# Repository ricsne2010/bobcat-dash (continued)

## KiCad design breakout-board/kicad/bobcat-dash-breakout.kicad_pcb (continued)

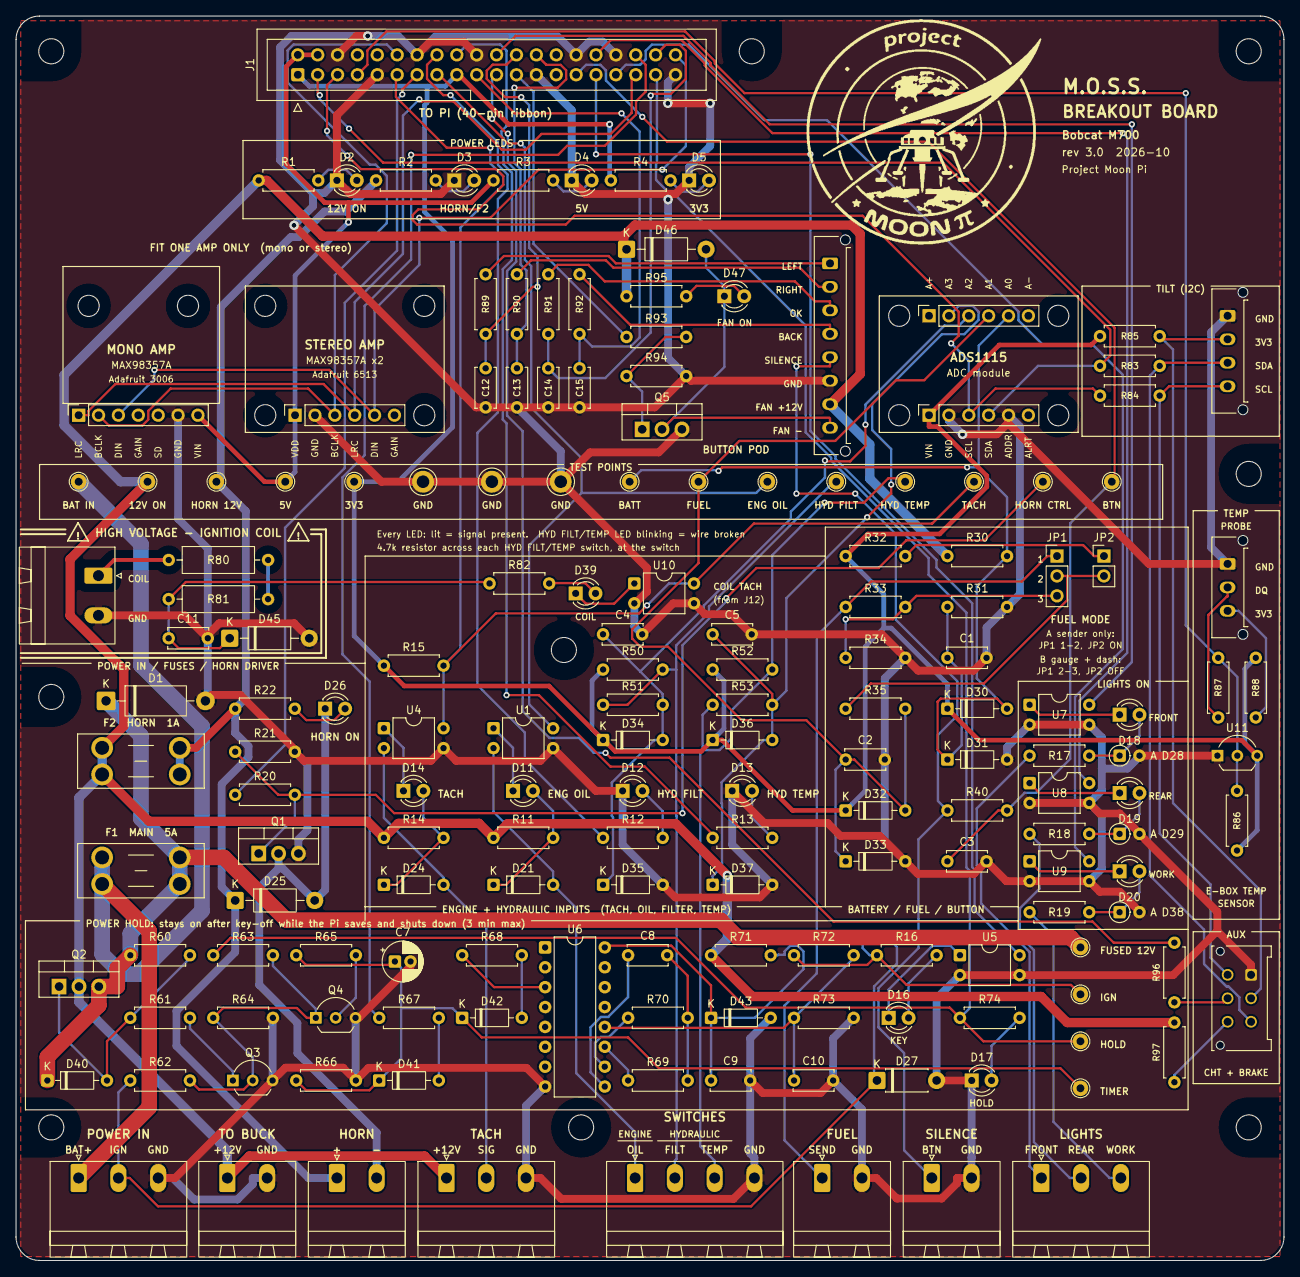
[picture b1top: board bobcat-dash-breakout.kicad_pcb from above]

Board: 2 copper layers, 162.0 x 159.0 mm, 187 parts (0 on the bottom side), 103 nets.

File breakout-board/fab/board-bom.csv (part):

"Refs","Value","Footprint","Qty","Description"
"C1,C2,C3,C4,C5,C9,C10,C12,C13,C14,C15","100nF","Capacitor_THT:C_Disc_D5.0mm_W2.5mm_P5.00mm","11","BACK button: debounce / noise filter,Debounce / noise filter,Decoupling,Filter,LEFT button: debounce / noise filter,OK button: debounce / noise filter,RIGHT button: debounce / noise filter"
"C7","10uF 25V","Capacitor_THT:CP_Radial_D5.0mm_P2.00mm","1","Stretches a power cut to a few seconds"
"C8","100nF film","Capacitor_THT:C_Disc_D5.0mm_W2.5mm_P5.00mm","1","Timing capacitor (film for accuracy)"
"C11","1uF 50V","Capacitor_THT:C_Disc_D5.0mm_W2.5mm_P5.00mm","1","Filters the coil's ringing: one clean pulse per spark (ceramic, X7R)"
"D1","P6KE20A","Diode_THT:D_DO-15_P12.70mm_Horizontal","1","TVS: clamps spikes, blows F1 if wired backwards"
"D2,D3,D4,D5,D17,D47","LED_green","LED_THT:LED_D3.0mm","6","+3.3V from Pi present,+5V from Pi present,Board powered (+12V switched on),Horn feed present (F2 OK),Pi is holding power on,Pod fan ON"
"D11,D12,D13,D14,D16,D18,D19,D20,D39","LED_yellow","LED_THT:LED_D3.0mm","9","Coil input: on while the coil is not charging, flickers with the engine,FILT: on = active, blink = wire fault (driven by the Pi),Front light on,Key on,OIL input active,Rear light on,TACH input active,TEMP: on = active, blink = wire fault (driven by the Pi),Work light on"
"D21,D24,D41,D42","1N4148","Diode_THT:D_DO-35_SOD27_P7.62mm_Horizontal","4","Pi KILL -> power cut,Reverse-spike protection across the LEDs,Timer -> power cut"
"D25,D46","1N4007","Diode_THT:D_DO-41_SOD81_P10.16mm_Horizontal","2","Flyback (coil horn / relay),Flyback (fan motor)"
"D26","LED_red","LED_THT:LED_D3.0mm","1","Horn output ON"
"D27","1N4007","Diode_THT:D_DO-41_SOD81_P7.62mm_Horizontal","1","Clamps negative spikes on the IGN wire"
"D28,D29,D38","1N4148","Diode_THT:D_DO-35_SOD27_P2.54mm_Vertical_AnodeUp","3","Reverse-spike protection across the LEDs (standing diode)"
"D30,D31,D32,D33,D34,D35,D36,D37","BAT85","Diode_THT:D_DO-35_SOD27_P7.62mm_Horizontal","8","Schottky clamp to 3.3V,Schottky clamp to GND"
"D40","BZX79C15","Diode_THT:D_DO-35_SOD27_P7.62mm_Horizontal","1","15 V zener: limits gate-source voltage"
"D43","BZX79C10","Diode_THT:D_DO-35_SOD27_P7.62mm_Horizontal","1","10 V supply for U6"
"D45","1N4744A","Diode_THT:D_DO-41_SOD81_P10.16mm_Horizontal","1","15 V 1 W zener: clamps the coil spike (and negative ringing to -0.7 V)"
"F1","5A","Fuse:Fuseholder_Blade_Mini_Keystone_3568","1","Mini blade fuse: main feed"
"F2","1A","Fuse:Fuseholder_Blade_Mini_Keystone_3568","1","Mini blade fuse: horn"
"J1","TO PI (40-pin ribbon)","Connector_IDC:IDC-Header_2x20_P2.54mm_Vertical","1","Box header, straight 40-pin IDC ribbon to the Pi GPIO header"
"J2","POWER IN","Connector_Phoenix_MSTB:PhoenixContact_MSTBA_2,5_3-G-5,08_1x03_P5.08mm_Horizontal","1","Constant battery +12V (fused at the battery), key switch IGN signal, chassis ground"
"J3","TO 5V BUCK","Connector_Phoenix_MSTB:PhoenixContact_MSTBA_2,5_2-G-5,08_1x02_P5.08mm_Horizontal","1","Switched, fused +12V out to the 12V->5V buck"
"J4","SWITCHES","Connector_Phoenix_MSTB:PhoenixContact_MSTBA_2,5_4-G-5,08_1x04_P5.08mm_Horizontal","1","Engine oil pressure, hydraulic filter bypass, hydraulic oil temp switch wires"
"J5","TACH","Connector_Phoenix_MSTB:PhoenixContact_MSTBA_2,5_3-G-5,08_1x03_P5.08mm_Horizontal","1","Hall sensor (brown +12V, black SIG, blue GND), if used instead of the coil input"
"J6","FUEL","Connector_Phoenix_MSTB:PhoenixContact_MSTBA_2,5_2-G-5,08_1x02_P5.08mm_Horizontal","1","Fuel sender"
"J7","HORN","Connector_Phoenix_MSTB:PhoenixContact_MSTBA_2,5_2-G-5,08_1x02_P5.08mm_Horizontal","1","Piezo alarm + and -"
"J8","SILENCE","Connector_Phoenix_MSTB:PhoenixContact_MSTBA_2,5_2-G-5,08_1x02_P5.08mm_Horizontal","1","Silence push button"
"J9","MAX98357A MONO","Connector_PinSocket_2.54mm:PinSocket_1x07_P2.54mm_Vertical","1","Socket for the mono MAX98357A I2S amp board (Adafruit 3006): LRC BCLK DIN GAIN SD GND VIN"
"J10","ADS1115 PWR/I2C","Connector_PinSocket_2.54mm:PinSocket_1x06_P2.54mm_Vertical","1","Socket for the ADS1115 board's bottom row: VIN GND SCL SDA ADDR ALRT (ADDR to GND: address 0x48)"
"J11","LIGHTS","Connector_Phoenix_MSTB:PhoenixContact_MSTBA_2,5_3-G-5,08_1x03_P5.08mm_Horizontal","1","Sense wires from the lamp side of the front / rear / work light switches (a few mA each)"
"J12","COIL","Connector_Phoenix_MSTB:PhoenixContact_MSTBA_2,5_2-G-5,08_1x02_P5.08mm_Horizontal","1","Ignition coil NEGATIVE terminal (high voltage spikes) + GND for a shielded wire's drain (rev 2.4)"
"J13","TILT","Connector_Molex:Molex_Micro-Fit_3.0_43650-0415_1x04_P3.00mm_Vertical","1","Molex Micro-Fit 3.0 43650-0415 (latching). Mates with housing 43645-0400 + 43030-0007 pins. Tilt sensor: GND, 3V3, SDA, SCL; cable under ~30-50 cm"
"J14","TEMP PROBE","Connector_Molex:Molex_Micro-Fit_3.0_43650-0315_1x03_P3.00mm_Vertical","1","Molex Micro-Fit 3.0 43650-0315 (latching): external DS18B20 probes: 1 GND, 2 DQ, 3 3V3. Housing 43645-0300"
"J15","ADS1115 INPUTS","Connector_PinSocket_2.54mm:PinSocket_1x06_P2.54mm_Vertical","1","Socket for the ADS1115 board's top row: A+ A3 A2 A1 A0 A-"
"J16","MAX98357A STEREO","Connector_PinSocket_2.54mm:PinSocket_1x06_P2.54mm_Vertical","1","Socket for the stereo MAX98357A amp board (Adafruit 6513): VDD GND BCLK LRC DIN GAIN. Fit J9 or J16, not both"
"J17","POD","Connector_Molex:Molex_Micro-Fit_3.0_43650-0815_1x08_P3.00mm_Vertical","1","Latching Molex Micro-Fit 3.0 8-pin to the button pod: LEFT RIGHT OK BACK SILENCE GND FAN+ FAN-"
"J18","AUX (CHT + BRAKE)","Connector_Molex:Molex_Micro-Fit_3.0_43045-0612_2x03_P3.00mm_Vertical","1","Molex Micro-Fit 3.0 43045-0612 2x3 (latching): CHT board. 1 GND, 2 3V3, 3 SDA, 4 SCL, 5 BRAKE, 6 BRAKE 12V. Housing 43025-0600"
"JP1","A=1-2  B=2-3","Connector_PinHeader_2.54mm:PinHeader_1x03_P2.54mm_Vertical","1","Fuel mode select"
"JP2","PULL-UP (A only)","Connector_PinHeader_2.54mm:PinHeader_1x02_P2.54mm_Vertical","1","Fit for option A"
"Q1,Q5","IRLZ44N","Package_TO_SOT_THT:TO-220-3_Vertical","2","Logic-level MOSFET, low-side switch,Logic-level MOSFET: pod fan, low-side switch"
"Q2","IRF4905","Package_TO_SOT_THT:TO-220-3_Vertical","1","P-MOSFET high-side power switch, -55 V 74 A 20 mOhm"
"Q3,Q4","BC547B","Package_TO_SOT_THT:TO-92_Inline_Wide","2","Power cut: overrides key and HOLD,Turns Q2 on"
"R1,R2,R22,R95","3.3k","Resistor_THT:R_Axial_DIN0207_L6.3mm_D2.5mm_P7.62mm_Horizontal","4",""
"R3,R35,R40,R67,R68,R89,R90,R91,R92,R96","1k","Resistor_THT:R_Axial_DIN0207_L6.3mm_D2.5mm_P7.62mm_Horizontal","10","BACK button: series protection,LEFT button: series protection,OK button: series protection,Parking brake signal: series protection (GPIO 9),RIGHT button: series protection,Series,Series protection"
"R4,R12,R13,R71,R74,R82","470","Resistor_THT:R_Axial_DIN0207_L6.3mm_D2.5mm_P7.62mm_Horizontal","6","LED current,LED current, ~2 mA,Status LED current,Supply"
"R11,R14,R16,R17,R18,R19,R97","2.2k","Resistor_THT:R_Axial_DIN0207_L6.3mm_D2.5mm_P7.62mm_Horizontal","7","LED current, ~4 mA,Parking brake input LEDs on the CHT board, ~4 mA; a shorted cable draws ~5 mA"
"R15,R21,R31,R34,R51,R53,R63,R72,R94","10k","Resistor_THT:R_Axial_DIN0207_L6.3mm_D2.5mm_P7.62mm_Horizontal","9","Divider bottom,Divider bottom (option B),Keeps the fan off while the Pi boots,Key on -> timer reset,Pi HOLD -> power on,Pull-down: horn off while the Pi boots,Series protection,Tach pull-up (10k from rev 2.4: halves the current the PC817s must sink, for margin at low LED current)"
"R20,R83,R84,R87,R93","100","Resistor_THT:R_Axial_DIN0207_L6.3mm_D2.5mm_P7.62mm_Horizontal","5","Gate resistor,Probe data series protection,SCL series protection,SDA series protection"
"R30,R33,R60,R62","47k","Resistor_THT:R_Axial_DIN0207_L6.3mm_D2.5mm_P7.62mm_Horizontal","4","Divider top (option B),Divider top (ratio 5.7),Gate pull-up: Q2 off by default,Key on -> power on"
"R32","220","Resistor_THT:R_Axial_DIN0207_L6.3mm_D2.5mm_P7.62mm_Horizontal","1","Sender pull-up (option A)"
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
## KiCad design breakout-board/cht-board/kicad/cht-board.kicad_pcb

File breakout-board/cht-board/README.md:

# CHT + Parking Brake Board (rev 1.0)

A small board (87 × 46 mm) for the electronics box, on a short latching cable to the breakout board's
**AUX** plug (J18, breakout board rev 3.0). It carries:

- **Cylinder head temperatures (CHT):** up to four Adafruit **MCP9601** thermocouple amplifier modules
  (product 5165), one per cylinder, plugged into sockets. Fit only the ones you need.
- **Parking brake input:** the switch on the handle comes in on a 2-pin Phoenix plug, through an optocoupler,
  to the Pi (GPIO 9). Green **BRAKE SET** LED while the brake is set.

## Thermocouples

- Sensor: The Sensor Connection **CHT-FS-072-06-18-K-MP** (or -120- / custom 144 in lead): Type K, ungrounded,
  18 mm ring for the Wisconsin VH4D's plugs, rated to 1000 °C.
- Each module has its own 2-screw terminal: the Type K wire (or Type K extension wire) goes **straight into it**.
  That terminal is the cold junction, right beside the chip that measures it, so there's nothing in between.
  US colours: **yellow +, red −** (the module marks + and −).
- Only Type K extension wire and Type K (yellow) mini connectors between the sensor and the module. For the
  box wall, panel-mount mini K jacks, then a short piece of K wire inside to the module.

## Addresses

The socket sets each module's I2C address through its ADDR pin, the same way the module's own address jumpers
do, so **leave the modules' 22k / 43k jumpers open** and any module works in any socket:

| Socket | Cylinder | ADDR | Address | `config.toml` |
|---|---|---|---|---|
| M1 | 1 | to GND | 0x60 | `{ name = "1", address = 0x60 }` |
| M2 | 2 | 22k to GND (R1) | 0x65 | `{ name = "2", address = 0x65 }` |
| M3 | 3 | 43k to GND (R2) | 0x66 | `{ name = "3", address = 0x66 }` |
| M4 | 4 | open | 0x67 | `{ name = "4", address = 0x67 }` |

List the fitted ones in `[cht] cylinders`. With one sensor, put its module in the socket for that cylinder.

## Parking brake

`J2 PARK BRAKE`: **SW** and **GND**. A sealed switch on the handle that **closes when the brake is set**
(e.g. a sealed roller-lever microswitch, IP67, with a factory pigtail; a weather-sealed Deutsch DT 2-pin at the
handle). Then `[park_brake] enabled = true`. The 12 V comes from the breakout board through 2.2k (R97), so the
cable can't draw more than ~5 mA even shorted.

## Assembly

- Modules: solder the 9-pin header that comes with each module **pins down**, plug it into the socket, and screw
  its two holes down on **11 mm M2.5 standoffs** (the holes are on the terminal edge).
- Board: four **M3** corner holes. The AUX cable: two Molex Micro-Fit 3.0 2×3 housings (43025-0600) and
  six crimp pins (43030-0007), **pin 1 to pin 1** straight through.
- The modules' SDA / SCL each have a 10k pull-up; with four of them on the bus the total is still fine for the
  Pi's I2C at 100 kHz.

## Files

- `kicad/`: KiCad 10 project (schematic + board), made by `generator/` (`bash generator/build.sh`, reusing the
  breakout board's `route.py`).
- `fab/cht-board-gerbers.zip` for PCBWay (blue mask, like the breakout board), `fab/cht-board-bom.csv`.
- `docs/`: schematic PDF and renders.

Module pinout from Adafruit's design files (Adafruit-MCP9601-PCB, header JP3): VIN GND SCL SDA ALERT1-4 ADDR.

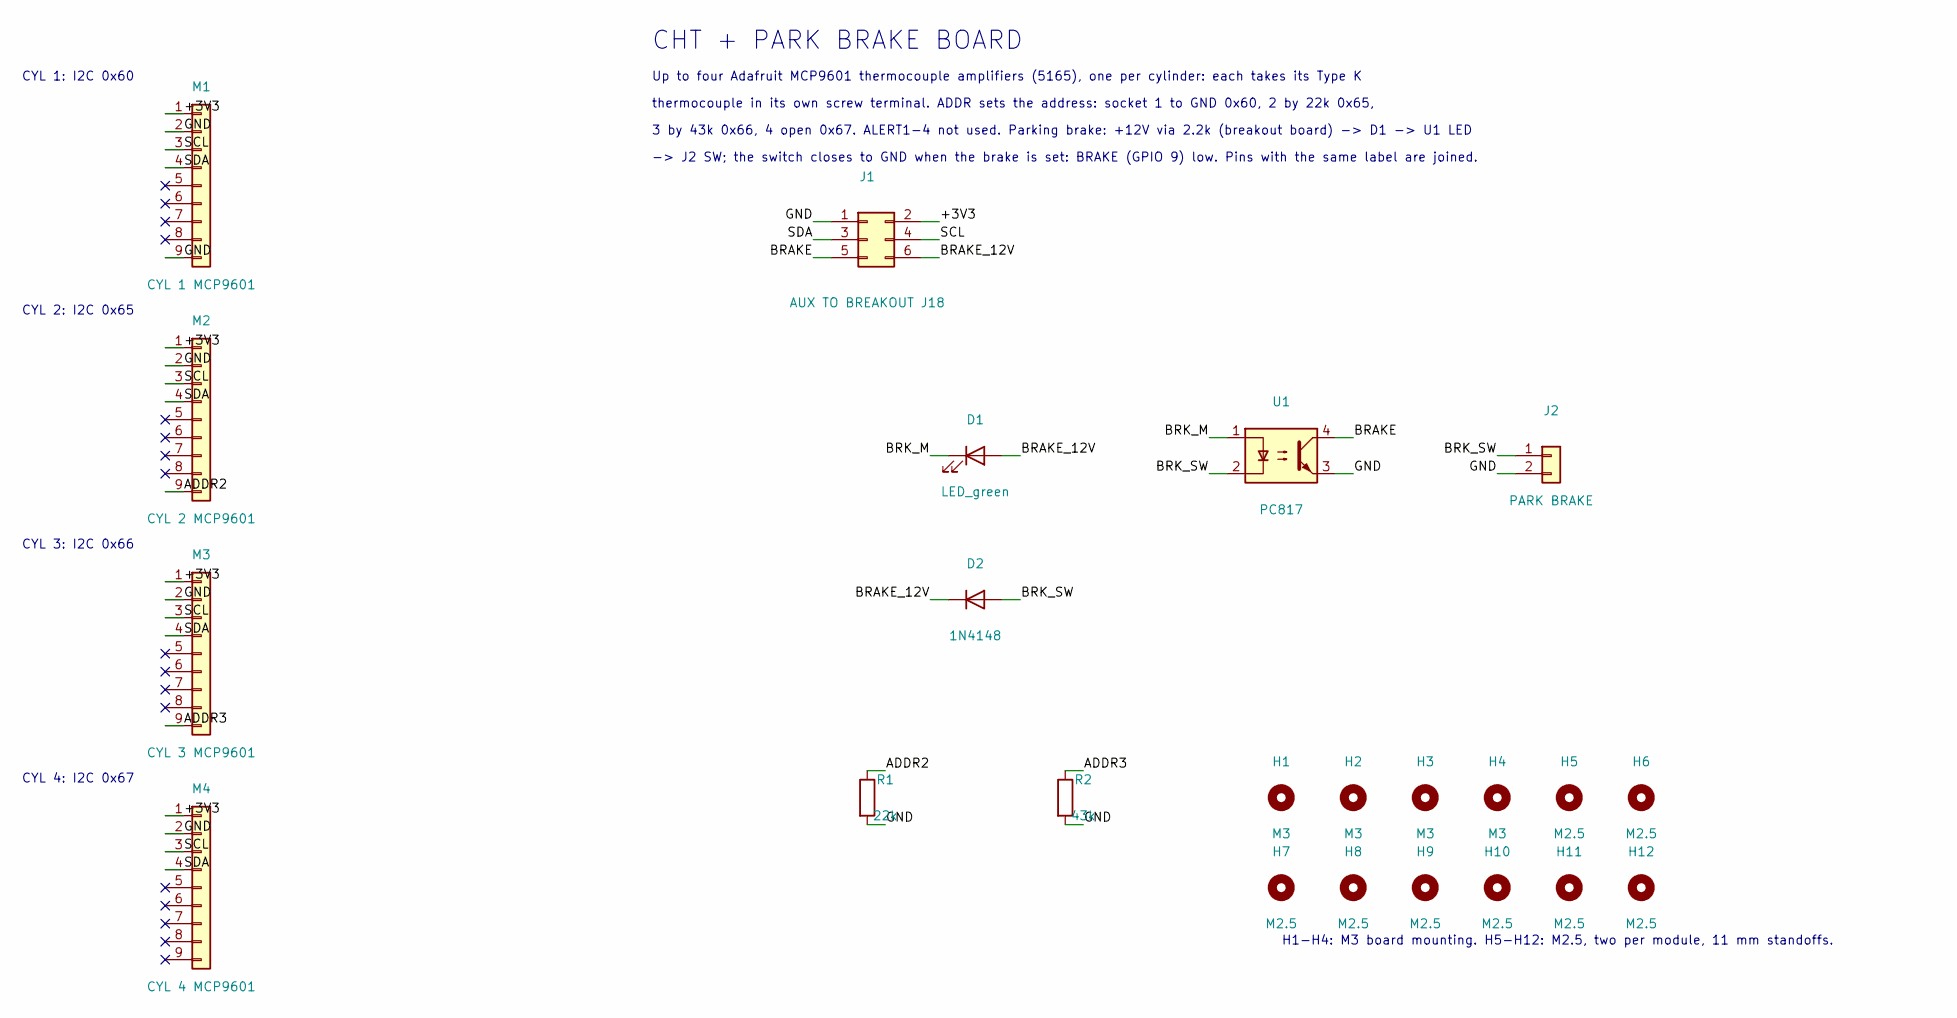
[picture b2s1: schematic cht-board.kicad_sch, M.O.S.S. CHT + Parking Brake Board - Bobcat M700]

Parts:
D1: LED_green; LED_D3.0mm
D2: 1N4148; D_DO-35_SOD27_P7.62mm_Horizontal
H1, H2, H3, H4: M3; MountingHole_3.2mm_M3
H5, H6, H7, H8, H9, H10, H11, H12: M2.5; MountingHole_2.7mm_M2.5
J1: AUX TO BREAKOUT J18; Molex_Micro-Fit_3.0_43045-0612_2x03_P3.00mm_Vertical
J2: PARK BRAKE; PhoenixContact_MSTBA_2,5_2-G-5,08_1x02_P5.08mm_Horizontal
M1: CYL 1 MCP9601; PinSocket_1x09_P2.54mm_Vertical
M2: CYL 2 MCP9601; PinSocket_1x09_P2.54mm_Vertical
M3: CYL 3 MCP9601; PinSocket_1x09_P2.54mm_Vertical
M4: CYL 4 MCP9601; PinSocket_1x09_P2.54mm_Vertical
R1: 22k; R_Axial_DIN0207_L6.3mm_D2.5mm_P7.62mm_Horizontal
R2: 43k; R_Axial_DIN0207_L6.3mm_D2.5mm_P7.62mm_Horizontal
U1: PC817; DIP-4_W7.62mm

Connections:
/+3V3: J1.2, M1.1, M2.1, M3.1, M4.1
/ADDR2: M2.9, R1.1
/ADDR3: M3.9, R2.1
/BRAKE: J1.5, U1.4
/BRAKE_12V: D1.2 (A), D2.1 (K), J1.6
/BRK_M: D1.1 (K), U1.1
/BRK_SW: D2.2 (A), J2.1, U1.2
/GND: J1.1, J2.2, M1.2, M1.9, M2.2, M3.2, M4.2, R1.2, R2.2, U1.3
/SCL: J1.4, M1.3, M2.3, M3.3, M4.3
/SDA: J1.3, M1.4, M2.4, M3.4, M4.4

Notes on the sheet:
CYL 1: I2C 0x60
CYL 2: I2C 0x65
CYL 3: I2C 0x66
CYL 4: I2C 0x67
CHT + PARK BRAKE BOARD
Up to four Adafruit MCP9601 thermocouple amplifiers (5165), one per cylinder: each takes its Type K
thermocouple in its own screw terminal. ADDR sets the address: socket 1 to GND 0x60, 2 by 22k 0x65,
3 by 43k 0x66, 4 open 0x67. ALERT1-4 not used. Parking brake: +12V via 2.2k (breakout board) -> D1 -> U1 LED
-> J2 SW; the switch closes to GND when the brake is set: BRAKE (GPIO 9) low. Pins with the same label are joined.
H1-H4: M3 board mounting. H5-H12: M2.5, two per module, 11 mm standoffs.

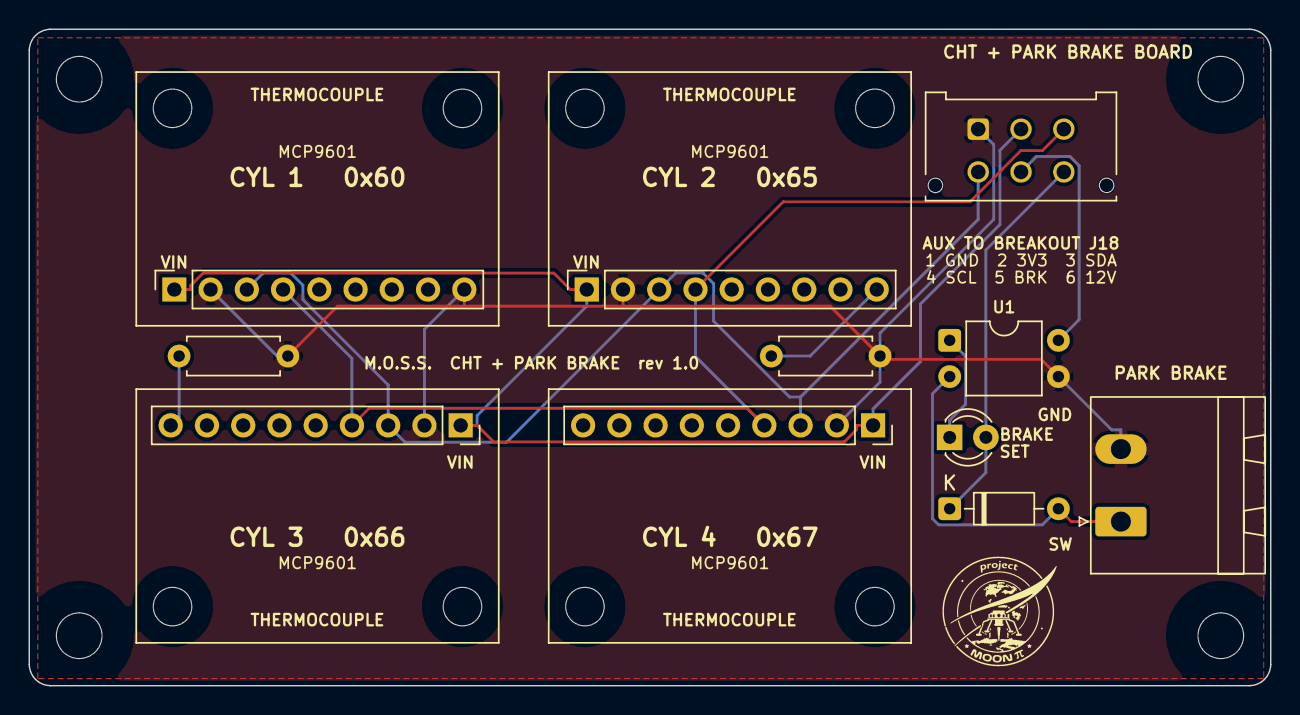
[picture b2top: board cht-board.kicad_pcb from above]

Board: 2 copper layers, 87.0 x 46.0 mm, 23 parts (0 on the bottom side), 10 nets.

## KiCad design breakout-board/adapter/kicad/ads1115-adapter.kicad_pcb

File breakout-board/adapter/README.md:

# ADS1115 Adapter (rev 1.1)

The breakout board (rev 2.8) takes the **current Adafruit ADS1115 (product 1085, STEMMA QT version)** directly:
two 6-pin rows 12.7 mm (0.5") apart, plugged into **J15** and **J10** and screwed down on H5–H8.

If that board isn't available, this adapter takes the other common ADS1115 layout: **one 10-pin row** in the order
`VDD GND SCL SDA ADDR ALRT A0 A1 A2 A3`. That's the older Adafruit 1085 and nearly every clone. Check the labels
on your module match that order before plugging it in.

- **Underneath:** male pins in the same two-row pattern as the Adafruit board (J1 into the breakout board's J15,
  J2 into its J10), and the same four M2.5 holes, so it sits on the same 11 mm standoffs.
- **On top:** a 10-pin female socket (J3) for the module, and two M2.5 holes (H5, H6) for the module's own
  mounting holes, so it's screwed down too, not just held by its pins. They match the original Adafruit 10-pin
  board (holes on its far edge, 12.7 mm from its pins, in line with pins 1 and 10). Clones vary: check yours.
- **Wiring is straight through:** same signals, same address (0x48: ADDR is grounded on the breakout board),
  **no software change**. A+ / A- of the two-row pattern aren't used.

| | |
|---|---|
| Size | 42 × 24.7 mm, 2 layers, 1.6 mm. The right-hand 12 mm carries the Project Moon Pi logo, top and back (beside the module, so it stays visible); on the breakout board it sits over the empty space between the ADC module and the TEMP column |
| Schematic | [docs/schematic.pdf](docs/schematic.pdf) |
| Gerbers | [fab/ads1115-adapter-gerbers.zip](fab/ads1115-adapter-gerbers.zip): order it with the main board (most makers sell 5 minimum for a few dollars) |
| KiCad files | [kicad/](kicad/) |

## Parts

| Qty | Part | Notes |
|---|---|---|
| 1 | Bare adapter PCB | `fab/ads1115-adapter-gerbers.zip` |
| 2 | Male pin header, 1×6, 2.54 mm, straight | J1, J2: soldered from **underneath** (plastic under the board, short pins through the top) |
| 1 | Female socket, 1×10, 2.54 mm, straight | J3, on top |
| 4 + 8 | M2.5 standoff, 11 mm, female–female + M2.5 × 5 mm screws | The same as for the Adafruit board: H1–H4 line up with the breakout board's H5–H8 |
| 2 + 4 | M2.5 standoff, female–female + M2.5 × 5 mm screws, for the module | H5, H6. Height = the socket + the module's header plastic, measured with it seated (about 11 mm) |

## Fitting it

1. Solder J1 and J2 with the adapter **plugged into the breakout board's sockets**, so the pins line up.
   The square pads are pin 1 on both boards.
2. Fit the module's two standoffs to H5 / H6 now: their screws go in from underneath, which you can't reach
   once the adapter is on the board.
3. Screw the adapter down on its four standoffs (H1–H4 onto the breakout board's H5–H8). Do this **before**
   fitting the module: the module covers those screws.
4. Plug the 10-pin module into J3 (pin 1, VDD, at the square pad, labels matching the silkscreen) and screw it
   to its standoffs. If a clone's holes don't line up, a dab of silicone or a cable tie keeps it from rattling.

## Rebuilding

`generator/build.sh` regenerates everything (schematic → board → routing with the breakout board's
`route.py` → ERC / DRC / parity), using KiCad 10 and Freerouting like the main board.

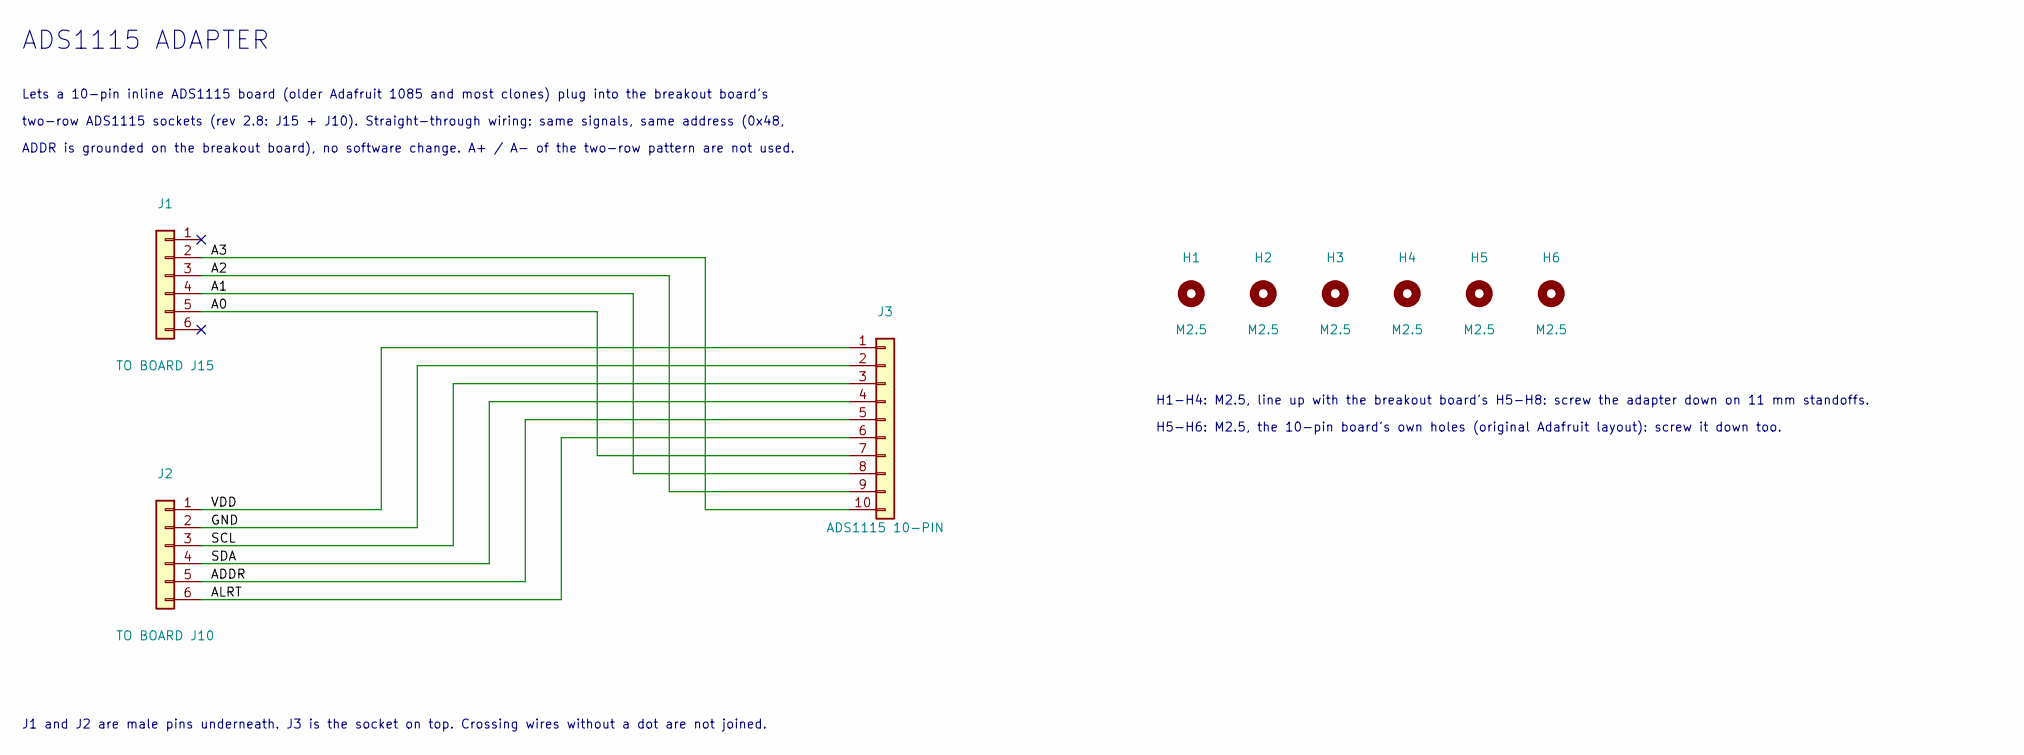
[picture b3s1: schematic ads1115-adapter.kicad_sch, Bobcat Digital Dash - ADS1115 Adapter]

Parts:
H1, H2, H3, H4, H5, H6: M2.5; MountingHole_2.7mm_M2.5
J1: TO BOARD J15; PinHeader_1x06_P2.54mm_Vertical
J2: TO BOARD J10; PinHeader_1x06_P2.54mm_Vertical
J3: ADS1115 10-PIN; PinSocket_1x10_P2.54mm_Vertical

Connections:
/A0: J1.5, J3.7
/A1: J1.4, J3.8
/A2: J1.3, J3.9
/A3: J1.2, J3.10
/ADDR: J2.5, J3.5
/ALRT: J2.6, J3.6
/GND: J2.2, J3.2
/SCL: J2.3, J3.3
/SDA: J2.4, J3.4
/VDD: J2.1, J3.1

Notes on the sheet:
ADS1115 ADAPTER
Lets a 10-pin inline ADS1115 board (older Adafruit 1085 and most clones) plug into the breakout board's
two-row ADS1115 sockets (rev 2.8: J15 + J10). Straight-through wiring: same signals, same address (0x48,
ADDR is grounded on the breakout board), no software change. A+ / A- of the two-row pattern are not used.
J1 and J2 are male pins underneath. J3 is the socket on top. Crossing wires without a dot are not joined.
H1-H4: M2.5, line up with the breakout board's H5-H8: screw the adapter down on 11 mm standoffs.
H5-H6: M2.5, the 10-pin board's own holes (original Adafruit layout): screw it down too.

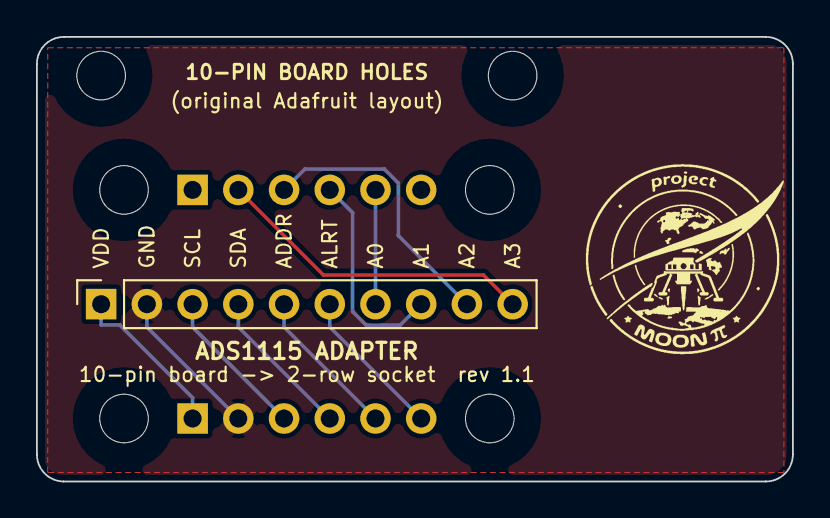
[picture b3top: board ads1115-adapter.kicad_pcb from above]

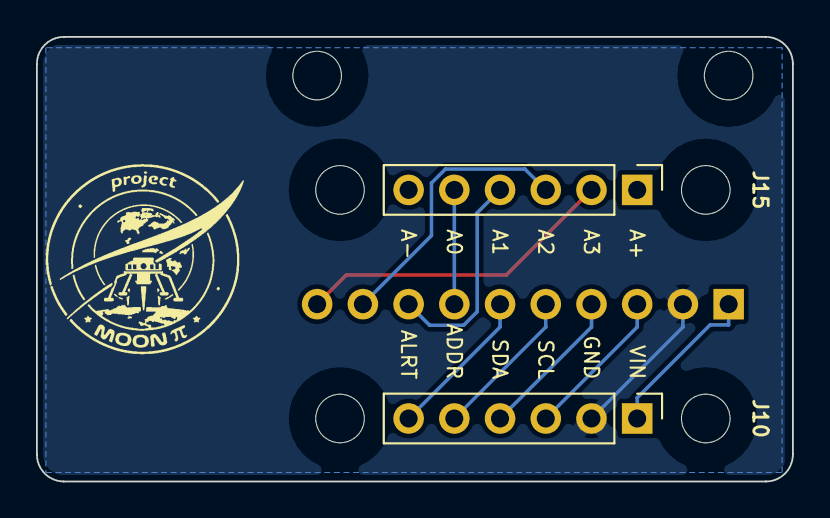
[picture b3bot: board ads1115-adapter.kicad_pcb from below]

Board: 2 copper layers, 42.0 x 24.7 mm, 9 parts (2 on the bottom side), 10 nets.

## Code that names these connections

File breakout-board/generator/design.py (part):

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TP = lambda ref, net, grp: part(ref, "Connector:TestPoint", net, FP_TP_GND if net == "GND" else FP_TP, {1: net}, grp, "test point")

# ---------------------------------------------------------------- Pi ribbon header (physical pin numbers)
PI = {1: "+3V3", 2: "+5V", 3: "SDA", 4: "+5V", 5: "SCL", 6: "GND", 7: "W1_DQ", 9: "GND", 11: "TACH_GPIO",
      12: "I2S_BCLK", 13: "HORN_GPIO", 14: "GND", 15: "OIL_GPIO", 16: "FILT_LED", 17: "+3V3",
      18: "TEMP_LED", 20: "GND", 22: "LT_FRONT_GPIO", 25: "GND", 29: "BTN_GPIO", 30: "GND", 31: "KEY_GPIO",
      32: "LT_REAR_GPIO", 33: "LT_WORK_GPIO", 34: "GND", 35: "I2S_LRC",
      19: "BTN_BACK_GPIO", 23: "FAN_GPIO", 24: "BTN_L_GPIO", 26: "BTN_R_GPIO", 38: "BTN_OK_GPIO",   # rev 2.9
      36: "KILL_GPIO", 37: "HOLD_GPIO", 39: "GND", 40: "I2S_DIN",
      21: "BRAKE_GPIO"}                                                                         # rev 3.0
part("J1", "Connector_Generic:Conn_02x20_Odd_Even", "TO PI (40-pin ribbon)",
     "Connector_IDC:IDC-Header_2x20_P2.54mm_Vertical",
     {n: PI.get(n) for n in range(1, 41)}, "pi", "Box header, straight 40-pin IDC ribbon to the Pi GPIO header")

# ---------------------------------------------------------------- harness connectors (vehicle side)
part("J2", "Connector_Generic:Conn_01x03", "POWER IN", mstb(3), {1: "+12V_IN", 2: "IGN", 3: "GND"}, "power",
     "Constant battery +12V (fused at the battery), key switch IGN signal, chassis ground")
part("J3", "Connector_Generic:Conn_01x02", "TO 5V BUCK", mstb(2), {1: "+12V", 2: "GND"}, "power", "Switched, fused +12V out to the 12V->5V buck")
part("J4", "Connector_Generic:Conn_01x04", "SWITCHES", mstb(4), {1: "OIL_SW", 2: "FILT_SW", 3: "TEMP_SW", 4: "GND"}, "switch", "Engine oil pressure, hydraulic filter bypass, hydraulic oil temp switch wires")
part("J5", "Connector_Generic:Conn_01x03", "TACH", mstb(3), {1: "+12V", 2: "TACH_SIG", 3: "GND"}, "tach",
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    C(f"C{12 + i}", "100nF", f"BTN_{b}_GPIO", "GND", "pod", f"{name} button: debounce / noise filter")
part("Q5", "Transistor_FET:IRLZ44N", "IRLZ44N", FP_TO220, {1: "FAN_G", 2: "FAN_DRAIN", 3: "GND"}, "pod",
     "Logic-level MOSFET: pod fan, low-side switch")
R("R93", "100", "FAN_GPIO", "FAN_G", "pod", "Gate resistor")
R("R94", "10k", "FAN_G", "GND", "pod", "Keeps the fan off while the Pi boots")
D("D46", "1N4007", "FAN_DRAIN", "+12V", FP_D41, "pod", "Flyback (fan motor)")
R("R95", "3.3k", "+12V", "FAN_LR", "pod")
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    LED(f"D{10 + i}", f"{name}_R", f"{name}_M", grp, f"{name} input active", "yellow")
    part(u, "Isolator:PC817", "PC817", FP_DIP4, {1: f"{name}_M", 2: sw, 3: "GND", 4: f"{name}_GPIO"}, grp, "Optocoupler")
    D(f"D{20 + i}", "1N4148", sw, f"{name}_R", FP_D35, grp, "Reverse-spike protection across the LEDs")
R("R15", "10k", "+3V3", "TACH_GPIO", "tach", "Tach pull-up (10k from rev 2.4: halves the current the PC817s must sink, for margin at low LED current)")

# ---------------------------------------------------------------- coil tach input (rev 2.2)
# Ignition coil negative terminal (PerTronix Ignitor + Flame-Thrower 40611, 3.0 ohm). It sits at ~1 V while
# the coil charges (dwell) and jumps to ~300-400 V when it fires, then settles at battery voltage.
# Two 2.2k 1/2 W resistors in series (each sees under 250 V) -> 15 V zener clamp + 1 uF filter
# -> 470 R -> yellow COIL LED -> PC817 -> GND. Coil open = LED on = TACH_GPIO low: one falling edge per spark.
# U10's output shares TACH_GPIO with U4 (Hall): wire one sensor or the other, not both.
# Rev 2.4: the coil wire has its own plug J12 on the left edge, and everything that sees the raw coil
# voltage (J12, R80, R81, plus the clamp D45/C11) sits in one boxed corner (group "hv").
part("R80", "Device:R", "2.2k 1/2W", "Resistor_THT:R_Axial_DIN0309_L9.0mm_D3.2mm_P12.70mm_Horizontal",
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C("C11", "1uF 50V", "COIL_CLAMP", "GND", "hv", "Filters the coil's ringing: one clean pulse per spark (ceramic, X7R)")
R("R82", "470", "COIL_CLAMP", "COIL_R", "tach", "LED current, ~2 mA")
LED("D39", "COIL_R", "COIL_M", "tach", "Coil input: on while the coil is not charging, flickers with the engine", "yellow")
part("U10", "Isolator:PC817", "PC817", FP_DIP4, {1: "COIL_M", 2: "GND", 3: "GND", 4: "TACH_GPIO"}, "tach",
     "Optocoupler: coil tach input")

# ---------------------------------------------------------------- monitored switches (filter, temp) -> A2, A3
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
# ---------------------------------------------------------------- horn driver
part("Q1", "Transistor_FET:IRLZ44N", "IRLZ44N", FP_TO220, {1: "HORN_G", 2: "HORN_DRAIN", 3: "GND"}, "horn", "Logic-level MOSFET, low-side switch")
R("R20", "100", "HORN_GPIO", "HORN_G", "horn", "Gate resistor")
R("R21", "10k", "HORN_G", "GND", "horn", "Pull-down: horn off while the Pi boots")
D("D25", "1N4007", "HORN_DRAIN", "+12V_HORN", FP_D41, "horn", "Flyback (coil horn / relay)")
R("R22", "3.3k", "+12V_HORN", "HORN_LR", "horn"); LED("D26", "HORN_LR", "HORN_DRAIN", "horn", "Horn output ON", "red")
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D("D33", "BAT85", "GND", "FUEL_ADC", FP_D35, "fuel", "Schottky clamp to GND")

# ---------------------------------------------------------------- aux analog + silence button
R("R40", "1k", "BTN_IN", "BTN_GPIO", "button", "Series protection")
C("C3", "100nF", "BTN_GPIO", "GND", "button", "Debounce / noise filter")

# ---------------------------------------------------------------- power hold (rev 2.0)
# +12V_BAT (constant, after F1) -> Q2 P-MOSFET -> +12V (everything else). Q2 is on while Q3 conducts.
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R("R61", "4.7k", "Q2_G", "Q3_C", "hold", "Gate drive (Vgs ~ -11 V)")
part("Q3", "Transistor_BJT:BC547", "BC547B", FP_TO92, {1: "Q3_C", 2: "PWR_ON", 3: "GND"}, "hold", "Turns Q2 on")
R("R62", "47k", "IGN", "PWR_ON", "hold", "Key on -> power on")
R("R63", "10k", "HOLD_GPIO", "PWR_ON", "hold", "Pi HOLD -> power on")
R("R64", "100k", "PWR_ON", "GND", "hold", "Pull-down")
part("Q4", "Transistor_BJT:BC547", "BC547B", FP_TO92, {1: "PWR_ON", 2: "KILL_B", 3: "GND"}, "hold", "Power cut: overrides key and HOLD")
R("R65", "100k", "KILL_RC", "KILL_B", "hold", "Q4 base (~20 uA: saturates Q4 with margin)")
R("R66", "1M", "KILL_RC", "GND", "hold", "Discharge")
part("C7", "Device:C_Polarized", "10uF 25V", FP_CP, {1: "KILL_RC", 2: "GND"}, "hold", "Stretches a power cut to a few seconds")
R("R67", "1k", "KILL_GPIO", "KILL_A", "hold", "Series")
D("D41", "1N4148", "KILL_A", "KILL_RC", FP_D35, "hold", "Pi KILL -> power cut")
R("R68", "1k", "TMR_Q14", "TMR_A", "hold", "Series")
D("D42", "1N4148", "TMR_A", "KILL_RC", FP_D35, "hold", "Timer -> power cut")
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R("R72", "10k", "IGN", "TMR_RST", "hold", "Key on -> timer reset")
R("R73", "100k", "TMR_RST", "GND", "hold", "Pull-down")
C("C10", "100nF", "TMR_RST", "GND", "hold", "Filter")
# key sense -> Pi: IGN -> 2.2k -> KEY LED -> PC817 -> GND. Key on = GPIO 6 low.
R("R16", "2.2k", "IGN", "KEY_R", "hold", "LED current, ~4 mA")
LED("D16", "KEY_R", "KEY_M", "hold", "Key on", "yellow")
part("U5", "Isolator:PC817", "PC817", FP_DIP4, {1: "KEY_M", 2: "GND", 3: "GND", 4: "KEY_GPIO"}, "hold", "Optocoupler: key sense")
D("D27", "1N4007", "GND", "IGN", "Diode_THT:D_DO-41_SOD81_P7.62mm_Horizontal", "hold", "Clamps negative spikes on the IGN wire")
R("R74", "470", "HOLD_GPIO", "HOLD_LK", "hold", "LED current")
LED("D17", "HOLD_LK", "GND", "hold", "Pi is holding power on", "green")
# schematic-only power flags (no footprint): U6 is the first part with power-input pins
part("#FLG01", "power:PWR_FLAG", "PWR_FLAG", None, {1: "TMR_VDD"}, "hold")
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     "Connector_Molex:Molex_Micro-Fit_3.0_43045-0612_2x03_P3.00mm_Vertical",
     {1: "GND", 2: "TILT_3V3", 3: "TILT_SDA", 4: "TILT_SCL", 5: "BRAKE_IO", 6: "BRAKE_12V"}, "aux",
     "Molex Micro-Fit 3.0 43045-0612 2x3 (latching): CHT board. 1 GND, 2 3V3, 3 SDA, 4 SCL, 5 BRAKE, 6 BRAKE 12V. Housing 43025-0600")
R("R96", "1k", "BRAKE_GPIO", "BRAKE_IO", "aux", "Parking brake signal: series protection (GPIO 9)")
R("R97", "2.2k", "+12V", "BRAKE_12V", "aux", "Parking brake input LEDs on the CHT board, ~4 mA; a shorted cable draws ~5 mA")

# ---------------------------------------------------------------- temperature (rev 2.7)
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
# ---------------------------------------------------------------- test points
TPS = ["+12V_IN", "+12V", "+12V_HORN", "+5V", "+3V3", "GND", "GND", "GND", "BATT_ADC", "FUEL_ADC",
       "OIL_GPIO", "FILT_SW", "TEMP_SW", "TACH_GPIO", "HORN_G", "BTN_GPIO"]
TPS += ["+12V_BAT", "IGN", "HOLD_GPIO", "KILL_RC"]     # rev 2.0: power hold
for i, n in enumerate(TPS, 1):
    TP(f"TP{i}", n, "tp")

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
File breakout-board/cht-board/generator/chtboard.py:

"""CHT + parking brake board (rev 1.0): sits in the electronics box beside the breakout board, on its AUX plug (J18).

* Four sockets for Adafruit MCP9601 thermocouple amplifier modules (product 5165): one per cylinder. Each
  module's own screw terminal takes the Type K thermocouple (or Type K extension wire): that's where the
  thermocouple metal meets copper, right beside the chip that measures its temperature (cold junction).
  Fit only the modules you need. The socket sets the module's I2C address with its ADDR pin, the same way the
  module's own 22k / 43k jumpers do: socket 1 to GND = 0x60, 2 through 22k = 0x65, 3 through 43k = 0x66,
  4 open = 0x67. Leave the modules' address jumpers open.
* The parking brake input: +12V (through 2.2k on the breakout board) -> BRAKE SET LED -> PC817 LED -> brake
  switch wire; the switch closes to chassis when the brake is set = GPIO 9 low. Like the breakout board's oil
  pressure input.

Module pinout (Adafruit-MCP9601-PCB, header JP3, left to right with the header at the bottom):
  VIN GND SCL SDA ALERT1 ALERT2 ALERT3 ALERT4 ADDR. Module 25.4 x 17.8 mm, M2.5 holes 2.54 mm in from the
  corners on the terminal-block edge. The modules stand on their headers in the sockets: 11 mm M2.5 standoffs.

Shared by gen_sch.py (schematic) and gen_pcb.py (board).
"""
NAME = "cht-board"
REV = "1.0"

MSTB2 = "Connector_Phoenix_MSTB:PhoenixContact_MSTBA_2,5_2-G-5,08_1x02_P5.08mm_Horizontal"
SOCKET9 = "Connector_PinSocket_2.54mm:PinSocket_1x09_P2.54mm_Vertical"
FP_R = "Resistor_THT:R_Axial_DIN0207_L6.3mm_D2.5mm_P7.62mm_Horizontal"
FP_LED = "LED_THT:LED_D3.0mm"
FP_D35 = "Diode_THT:D_DO-35_SOD27_P7.62mm_Horizontal"
FP_DIP4 = "Package_DIP:DIP-4_W7.62mm"

MODULE_PINS = ["VIN", "GND", "SCL", "SDA", "AL1", "AL2", "AL3", "AL4", "ADDR"]
ADDR = {1: "GND", 2: "ADDR2", 3: "ADDR3", 4: None}            # socket -> what its ADDR pin goes to
ADDRESS = {1: "0x60", 2: "0x65", 3: "0x66", 4: "0x67"}

# ref: (symbol, value, footprint, {pin: net or None}, description)
PARTS = {
    "J1": ("Connector_Generic:Conn_02x03_Odd_Even", "AUX TO BREAKOUT J18",
           "Connector_Molex:Molex_Micro-Fit_3.0_43045-0612_2x03_P3.00mm_Vertical",
           {1: "GND", 2: "+3V3", 3: "SDA", 4: "SCL", 5: "BRAKE", 6: "BRAKE_12V"},
           "Molex Micro-Fit 3.0 43045-0612 2x3 (latching): to the breakout board's AUX plug J18, pin to pin. "
           "1 GND, 2 3V3, 3 SDA, 4 SCL, 5 BRAKE (GPIO 9), 6 BRAKE 12V. Housing 43025-0600 both ends"),
    "J2": ("Connector_Generic:Conn_01x02", "PARK BRAKE", MSTB2, {1: "BRK_SW", 2: "GND"},
           "Phoenix MSTB 2-pin: parking brake switch (closed = brake set) between SW and GND"),
    "U1": ("Isolator:PC817", "PC817", FP_DIP4, {1: "BRK_M", 2: "BRK_SW", 3: "GND", 4: "BRAKE"},
           "Optocoupler: parking brake input"),
    "D1": ("Device:LED", "LED_green", FP_LED, {2: "BRAKE_12V", 1: "BRK_M"}, "BRAKE SET: lit while the brake is set"),
    "D2": ("Device:D", "1N4148", FP_D35, {2: "BRK_SW", 1: "BRAKE_12V"}, "Reverse-spike protection across the LEDs"),
    "R1": ("Device:R", "22k", FP_R, {1: "ADDR2", 2: "GND"}, "Socket 2 address: 0x65"),
    "R2": ("Device:R", "43k", FP_R, {1: "ADDR3", 2: "GND"}, "Socket 3 address: 0x66"),
}
for n in range(1, 5):
    pins = {1: "+3V3", 2: "GND", 3: "SCL", 4: "SDA", 5: None, 6: None, 7: None, 8: None, 9: ADDR[n]}
    PARTS[f"M{n}"] = ("Connector_Generic:Conn_01x09", f"CYL {n} MCP9601", SOCKET9, pins,
                      f"Socket for an Adafruit MCP9601 module (5165): cylinder {n}, I2C {ADDRESS[n]}. "
                      "VIN GND SCL SDA ALERT1-4 ADDR")
for i in range(1, 5):
    PARTS[f"H{i}"] = ("Mechanical:MountingHole", "M3", "MountingHole:MountingHole_3.2mm_M3", {}, "Board mounting hole")
for i in range(5, 13):
    PARTS[f"H{i}"] = ("Mechanical:MountingHole", "M2.5", "MountingHole:MountingHole_2.7mm_M2.5", {},
                      "Standoff hole for an MCP9601 module (11 mm M2.5 standoff)")

# ---------------------------------------------------------------- geometry (mm, y down)
W, H = 87.0, 46.0
MW, MH = 25.4, 17.78                        # module outline
# module top-left corners; "flip" = turned round so its header faces the middle of the board and its
# thermocouple terminal faces the board's edge (top row: terminals up, bottom row: terminals down)
MODULES = {1: (7.5, 3.0, False), 2: (36.4, 3.0, False), 3: (7.5, H - 3.0 - MH, True), 4: (36.4, H - 3.0 - MH, True)}


def module_pin(n, k):
    """Socket n's pin k (1 = VIN ... 9 = ADDR) position."""
    ox, oy, flip = MODULES[n]
    if flip:
        return ox + MW - 2.667 - 2.54 * (k - 1), oy + 2.54
    return ox + 2.667 + 2.54 * (k - 1), oy + 15.24


def module_holes(n):
    ox, oy, flip = MODULES[n]
    y = oy + (15.24 if flip else 2.54)
    return [(ox + 2.54, y), (ox + 22.86, y)]


BOARD_HOLES = [(3.5, 3.5), (W - 3.5, 3.5), (3.5, H - 3.5), (W - 3.5, H - 3.5)]
HOLES = BOARD_HOLES + [h for n in range(1, 5) for h in module_holes(n)]

# parts in the right-hand strip (x 63-87): pin 1 positions (rotations in gen_pcb). J2's plug faces the right edge.
STRIP = {"J1": (66.5, 7.0), "U1": (64.5, 21.8), "D1": (64.5, 28.6), "D2": (64.5, 33.6), "J2": (W - 10.5, 34.5)}
R_AT = {"R1": (52.0, 22.9, 0), "R2": (10.5, 22.9, 0)}       # in the gap between the module rows, by their sockets
LOGO_CENTRE, LOGO_WIDTH = (68.0, 40.8), 8.0
